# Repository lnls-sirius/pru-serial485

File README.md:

## PRUserial485 - _SIRIUS_
_PRU-based high performance serial communication_  

_Author:_  
Patricia H. Nallin ( _patricia.nallin@lnls.br_ )

_____

### Dependancies

* uio_pruss module
* prussdrv C library

_____

### Memory mapping

This applications reserves 2 MB from DDR memory via modprobe uio_pruss.
* 400 kB for sync curves
* 600 kB for FF application
* 1 MB for future needs

_____

### Building the library

Enter the folder `src` and run `make install`. This will compile PRU and host codes, install it to your Beaglebone and create a Python module to use these libraries.

_____

### Using the library

_**Before using it**_

1. Configure Beaglebone pins to PRU. Run `overlay.sh` script each time you restart your Beaglebone.

2. In your python-sirius (python3) code, you can just:
```python
import PRUserial485
```  
 It is not needed to copy any library files to your project.

---

#### Available Methods

_**General Purpose**_

- ```PRUserial485_open(int baudrate, char mode)```

   PRU initialization. Shared memory configuration and loading binaries into PRU.  
   * _baudrate:_  
   RS485 serial desired baudrate. Available: 9600, 14400, 19200, 38400, 57600, 115200 bps and 1, 6, 10, 12 Mbps
   * _mode:_  
   "M" for master, "S" for slave mode, and "P" for passive mode (receive-only, can never transmit).

- ```PRUserial485_address()```

   Gets SERIALxxCON board address (hardware defined)
   Returns: integer value (0 to 31)

- ```PRUserial485_close()```

   Closes PRUs and memory mapping.

- ```PRUserial485_write(bytes, float timeout)```

   Sending data through RS485 network  

   _*Parameters*_
  * _data:_  
  Python bytes containing values to be transmitted through serial network.
  * _timeout:_  
  Maximum waiting time to start getting an answer, in milliseconds (ms). Minimum: 15ns / Maximum: 64s. If 0, does not wait for response. ATTENTION: in slave mode, this parameter is ignored.  

  _*Return*_
  * _MASTER MODE:_  
   Returns only after response received (valid response, timeout or ignored)
  * _SLAVE MODE:_  
   Returns just after data completely sent.
  * _PASSIVE MODE:_  
   Always returns `ERR_PASSIVE_MODE_NO_SEND` immediately, without touching the bus. A passive-mode connection can never transmit; open in master or slave mode to send.

- ```PRUserial485_read(uint32_t nbytes)```

   Receiving data through RS485 network

   _*Parameters*_
  * _nbytes (OPTIONAL):_  
  Number of bytes to read. If empty or 0, all data will be read.
  If nbytes is greater than available bytes, return all available bytes. Note: This function does not block or wait for incoming data.   

   _*Return*_: bytes corresponding to data received.

- ```PRUserial485_read_flush()```

   Flush receive FIFO buffer.

_**Curves**_

- ```PRUserial485_curve(int block, [float_list curve1, float_list curve2, float_list curve3, float_list curve4])```

   Storing curves into memory. Each curve correspond to a power supply in the crate.   

   _*Parameters*_
  * _curveX:_  
  Python float list containing curve points, up to 6250 points. Curves must all have same length.
  * _block:_  
  Identification of block which will be loaded with curve points. (0 to 3)  

- ```PRUserial485_set_curve_block(int block)```

   Selection of block which will be performed in next cycle. Default value is 0.   

   _*Parameters*_
  * _block:_  
  Identification of block (0 to 3)  

- ```PRUserial485_read_curve_block()```

   Read block identification which will be performed in next cycle.    

   _*Returns*_: Block identification (0 to 3)

- ```PRUserial485_set_curve_pointer(int next_point)```

   Selection of point of curve that will be performed after the next sync pulse   

   _*Parameters*_
  * _next_point:_  
   index of next point (0 to (len(curve)-1))  

- ```PRUserial485_read_curve_pointer()```

   Read curve index (point) which will be sent in next sync pulse.    

   _*Returns*_: index of next point (0 to (len(curve)-1))

_**Sync Operation**_

- ```PRUserial485_sync_start(int sync_mode, float delay, int sync_address)```

   Sync mode operation.   

   _*Parameters*_
  * _sync_mode:_  
                 | 0x51 - Single curve sequence & Intercalated read messages  
                 | 0x5E - Single curve sequence & Read messages at End of curve  
                 | 0xC1 - Continuous curve sequence & Intercalated read messages  
                 | 0xCE - Continuous curve sequence & Read messages at End of curve  
                 | 0x5B - Single Sequence - Single Broadcast Function command
  * _delay:_  
  time between end of sync serial message and start of a normal message, when sending normal commands after sync pulses.
  * _sync_address:_  
  PS Controller address to which setpoints will be addressed to. Parameter only needed if sync_mode != 0x5B  

- ```PRUserial485_sync_stop()```

   Stops sync operation mode.   

- ```PRUserial485_sync_status()```

   Verifies whether PRU is waiting for a sync pulse or not    

   _*Returns*_: 1 if true, 0 if false

- ```PRUserial485_read_pulse_count_sync()```

   Read number of sync pulses already received.    

   _*Returns*_: counting value (0 to (2^32 - 1))

- ```PRUserial485_clear_pulse_count_sync()```

   Clears pulse counting registers. Action is only performed if sync mode is disabled.

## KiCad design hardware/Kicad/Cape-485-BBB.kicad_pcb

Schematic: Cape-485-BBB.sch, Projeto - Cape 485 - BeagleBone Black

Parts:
Beagle1: BeagleBone
C3, C4, C6, C7, C13: 0.1uF; C_0805
C5, C15: 1uF; C_0805
C8: 0.01uF; C_0805
C9, C11: 47n; C_0805
C10: 10u; C_0805
C12: Conn_SMA; SMA_Small
C14: 2.2uF; C_0805
C16: 100n; C_0805
D1: Led_Small; LED-0805
D2, D3, D4: LED; LED_0805
J1, J2: RJ25
JP3, JP4: Jumper_NO_Small; Test_Point
P10: CONN_02X05; Pin_Header_Straight_2x05
Q1, Q2, Q3: BSR14; SOT-23
R1: 50r; R_0805
R2, R9, R11: 1k; R_0805
R3: 620R; R_0805
R4, R8: 150r; R_0805
R10: 120r; R_0805
R12, R14, R16: 10k; R_0805
R13, R15, R17: 100r; R_0805
U1: MAX3107E; TSSOP-24_4.4x7.8mm_Pitch0.65mm
U3: IL3685; SOIC-16_7.5x10.3mm_Pitch1.27mm
U4: DCR01XXXXU; SOIC-28_7.5x17.9mm_Pitch1.27mm
U5, U6: TS5A21366
X1: OSCILADOR; Oscilador_3.3V_HCMOS_TTL_SMD

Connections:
+3V3: Beagle1.C3, Beagle1.C4, C3.1, C4.1, C6.2, C8.1, C9.2, P10.1, P10.3, P10.5, P10.7, P10.9, R2.1, U1.3 (Va), U1.5 (I2C'/SPI), U1.6 (LDOEN), U1.13 (VL), U1.23 (Vext), U3.1 (VDD1), X1.4 (VCC)
+5V: Beagle1.C7, Beagle1.C8, C14.1, D2.2 (A), D3.2 (A), D4.2 (A), R3.1, U4.1 (Vs), U4.2 (Vs)
+5VP: C10.1, C11.2, C13.1, C16.2, JP3.1, JP4.1, R4.2, U3.16 (VDD2), U4.14 (Vo), U5.8 (V+)
/1: Beagle1.B31, P10.2
/2: Beagle1.B32, P10.4
/4: Beagle1.B33, P10.6
/8: Beagle1.B34, P10.8
/16: Beagle1.B35, P10.10
/A: J1.2, J2.2, U3.12 (A), U5.2 (COM1)
/B: J1.3, J2.3, U3.13 (B), U5.5 (NO2)
/CTS': U1.19 (CTS'), U1.20 (RTS'/CLKOUT), U3.4 (RE), U3.5 (DE)
/LED1: Beagle1.B28, R12.2
/LED2: Beagle1.B29, R14.2
/LED3: Beagle1.B40, R16.2
/PRU0: Beagle1.B39, R2.2, U1.11 (IRQ')
/PRU2: Beagle1.B41, U1.10 (DIN/A1)
/PRU4: Beagle1.B43, U1.9 (CS'/A0)
/PRU6: Beagle1.B45, U1.8 (SCLK/SCL)
/PRU7: Beagle1.B46, U1.7 (DOUT/SDA)
/RX: U1.21 (RX), U3.3 (R)
/SYNC: Beagle1.B27, C12.1, R1.1
/SYS_RST: Beagle1.C10, C7.2, U1.12 (RST)
/TX: U1.22 (TX), U3.6 (D)
GNDA: Beagle1.B1, Beagle1.B2, Beagle1.C45, Beagle1.C46, C3.2, C4.2, C5.2, C6.1, C7.1, C8.2, C9.1, C12.2, C14.2, D1.1 (K), Q1.3 (E), Q2.3 (E), Q3.3 (E), R1.2, U1.2 (AGND), U1.14 (DGND), U3.2 (gnd1), U3.8 (gnd1), U4.26 (0VIN), U4.27 (0VIN), X1.2 (GND)
GNDREF: C10.2, C11.1, C13.2, C15.2, C16.1, J1.1, J1.4, J1.5, J2.1, J2.4, J2.5, R8.1, R9.2, R11.2, U3.9 (gnd2), U3.15 (gnd2), U4.13 (0VOUT), U5.4 (GND)
unnamed: C5.1, U1.4 (V18)
unnamed: C15.1, U4.12 (VREC), U4.16 (ENABLE)
unnamed: D1.2 (A), R3.2
unnamed: D2.1 (K), R13.1
unnamed: D3.1 (K), R15.1
unnamed: D4.1 (K), R17.1
unnamed: JP3.2, R9.1, U5.3 (IN2), U5.7 (IN1)
unnamed: JP4.2, R11.1
unnamed: Q1.1 (C), R13.2
unnamed: Q1.2 (B), R12.1
unnamed: Q2.1 (C), R15.2
unnamed: Q2.2 (B), R14.1
unnamed: Q3.1 (C), R17.2
unnamed: Q3.2 (B), R16.1
unnamed: R4.1, U5.1 (NO1)
unnamed: R8.2, U5.6 (COM2)
unnamed: U1.1 (XIN), X1.3 (OUT)

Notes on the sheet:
TERMINACAO 485
ENDERECO (MODO SLAVE)
Alimentação Isolada

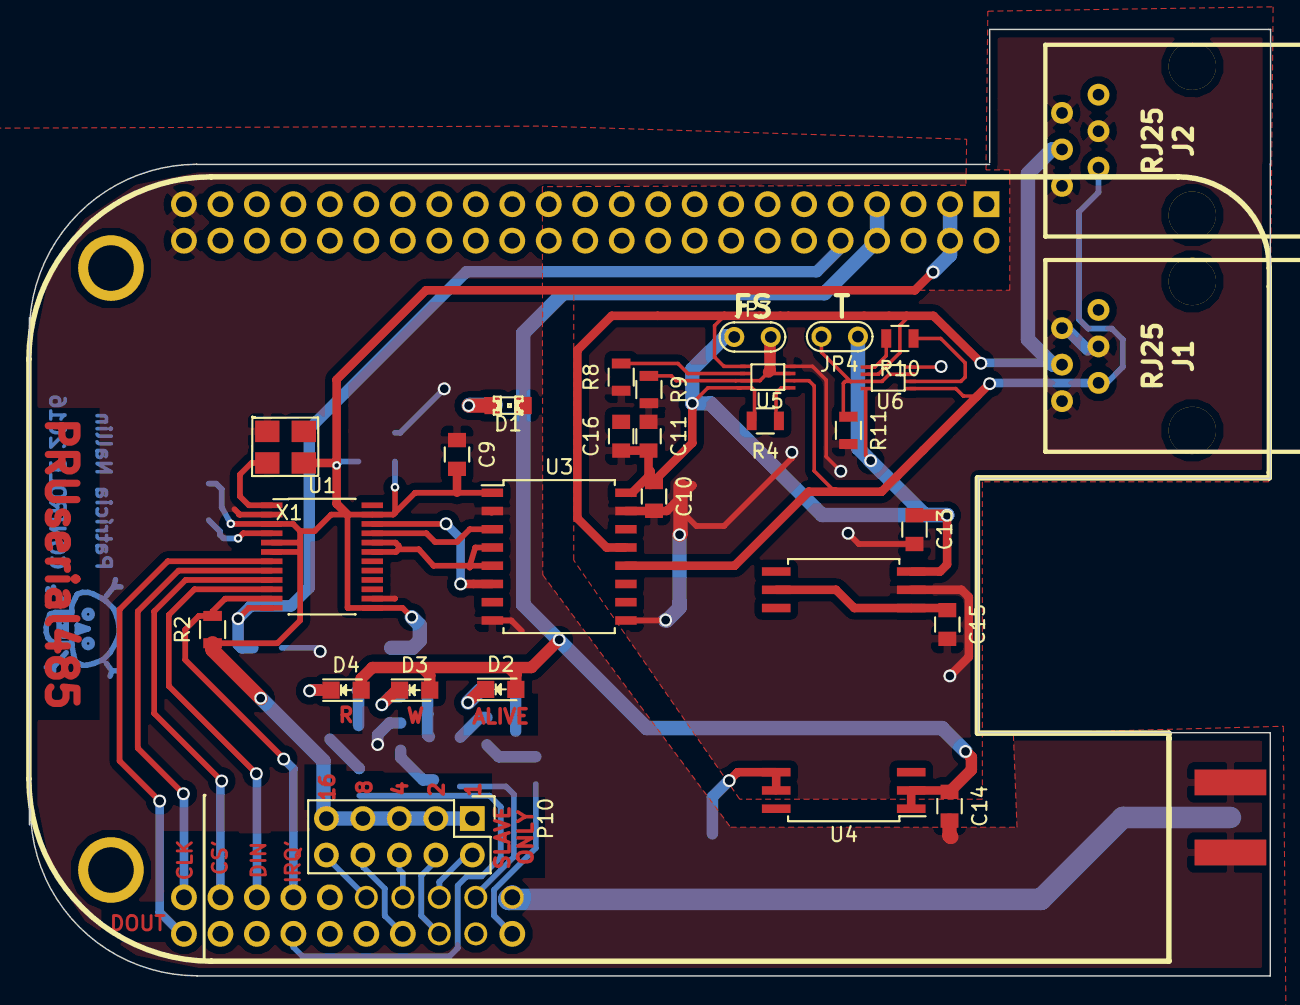
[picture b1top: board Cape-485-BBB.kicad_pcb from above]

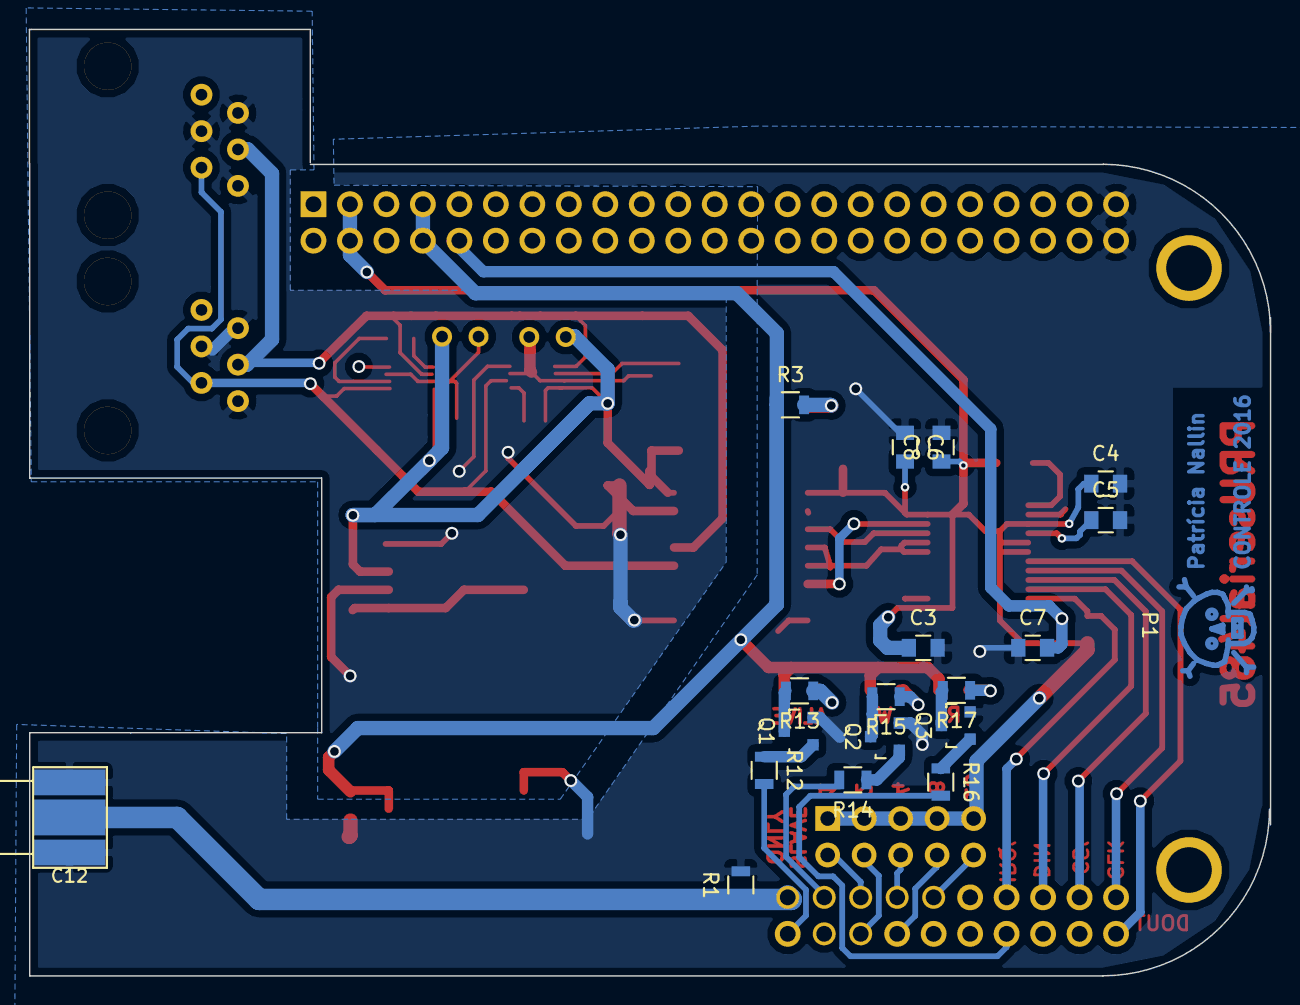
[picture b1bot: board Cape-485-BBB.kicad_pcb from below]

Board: 2 copper layers, 86.4 x 65.9 mm, 48 parts (19 on the bottom side), 42 nets.

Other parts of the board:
P1: CONN_01X01; Symbol_Danger_CopperTop_Small

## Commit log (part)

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2015-08-17 second commit
2015-08-17 Teste
2015-08-17 PRU commit 1
2015-08-17 PRU commit 2
2015-08-18 PRU firmware
2015-08-19 PRU firmware - BUG comando iniciar post-morten corrigido
2015-08-19 PRU firmware - Comando 08 corrigido / include adicionado / timeout em alto nivel
2015-08-20 PRU firmware atualizado
2015-08-20 Novo documento
2015-08-31 sync - borda de subida
2015-08-31 sync
2015-10-27 testing
2015-10-27 Hardware docs
2015-10-27 sem uso
2015-11-19 Nova versao: Serial485 Modo Master ou Slave
2015-12-10 Atulizado - linha de atualizacao do byte shram[1]
2015-12-10 update linha 423
2016-05-30 new hardware version
2016-05-30 new firmware version
2016-05-30 new installation doc version
2016-07-19 Update DTO for BBB and BBG
2016-08-12 added panels design
2016-08-31 Sync pulse counting added
2016-08-31 not necessasry
2016-08-31 not necessary
2016-11-04 Added info about timeout range
2016-11-04 Improving slave data transfer
2016-11-06 upgrades
2017-01-30 Minor changes on PRUserial485.p
2017-02-03 New performance for sync mode
2017-02-03 update data type on write method
2017-02-07 Update for choosing when to send normal messages on sync mode.
2017-02-07 Update sync and normal messages delay
2017-02-07 Update sync_start parameter
2017-02-07 Update for choosing time between sync and normal commands
2017-02-08 Update sync delay for usec
2017-02-08 PRUserial485_write. request must be a list of char
2017-02-08 Update sync instruction. Broadcasting (0xFF) function 12.
2017-02-21 Sync count on slave mode added.
2017-02-21 Update sync count for slave mode.
2017-02-22 Board hardware address updated. No more conflict.
2017-03-03 Update send function. Timeout type conversion is ok now
2017-03-22 Update PRUserial485_read(). Returns empty vector if buffer contains old data.
2017-03-22 Update set_sync_stop_PRU() function.
2017-04-28 Update Slave Receive instructions: Removed blinking LED and reads bytes in blocks of 16.
2017-04-28 New organizing folders and Python library is now installed on system
2017-05-03 setup.py added.
2017-05-25 Update error return on function "clear_pulse_count_sync()"
2018-01-25 Updated PRUserial485 library. Sync via setpoint and Python3 compatibility
2018-01-26 README file
2018-01-26 Test commit
2018-01-29 Update script to use sirius-python link
2018-01-29 Add gitignore file
2018-01-30 Adapt PRUserial485.py to pylama code conventions
2018-03-27 New version available
2018-04-10 Add __version__ attribute to package
    - this attribute is read from VERSION file and set.
    - rename PRUserial485.py to implementation.py to avoid package and module having the same name, thus avoiding potential problems.
    - Change return value of 'sync_status' to boolen type, instead of string.
2018-04-13 New version available. Updating curves on the fly in now implemented
2018-04-13 Minor changes
2018-04-14 Replace tab chars to spaces in python module
    - in order to avoid identation runtime error.
2018-04-14 Create a python module variable 'libraries_loaded'
    - to indicate whether all dynamical low-level PRU libraries were successfully loaded
    - catching the exception while ctype-importing the libraries allow for the PRUserial485 python library importation to happen in those situations where the PRU functions would never be invoked (simula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
2018-04-14 Clean package namespace
2018-04-17 Read me - first version
2018-04-17 Read me - first version available
2018-04-19 updating .sh scripts
2018-04-20 Add commit hash to package version
    - Add input to library_build.sh so that user can select 'install' (default if argument is not passed) or 'develop' for the python library.
2018-04-20 RS485 delay after sync pulse for 0x5C mode added
2018-04-27 Block # (curves) is now read at the beginning of curve
2018-04-27 Add *swp to gitignore
2018-04-28 Replace tabs for spaces in C files
2018-04-28 Comment out print statements in C code
    - Instead of print statements, we can use return values and a constant table
    to infer what the error was.
    - Fixed code identation.
2018-04-28 Add python namespace for return constants of C lib
2018-04-28 Fix bug introduced in last commit
2018-04-28 Add return codes table in C file too
2018-04-28 Minor code cleanup
2018-04-28 Fix conflict from last commit
2018-04-28 Code cleanup
    - Move table of return codes from .c to .h file
    - Sort order of fcuntions in .h according to order in .c
    - Added missing return docstrings in .h file.
2018-05-02 Bug corretions on signaling end of sync mode
2018-05-02 Change minor part of version number (bug fix)
2018-05-17 Changing sync mode code 0x5C to 0x5B
2018-05-17 Sync mode 0x5C moved to 0x5B
2018-05-17 README updated
2018-05-17 Update constants in python package
    - Update also code comments and docs with new sync mode code.
2018-05-17 Update bug-fix portion of package version number
2018-08-09 Both Python-Sirius and Python2 library building is now available
2018-09-20 new developments backup
2019-01-30 Bug correction on PRUserial485 high level library
    Bug on function PRUserial485_set_curve_pointer(int). Comparison before returning was always locking, once values were never identical (missing multiplication x16)
2019-08-06 Bug correction: commit hash at library version
2020-01-10 Improving python module performance
2020-01-13 renaming and improving prucon to pru-serial485
2020-01-13 hash version included
2020-01-13 code comments added
2020-01-13 first developments
2020-01-14 minor bugs correction
2020-01-21 Complete python module and README file
2020-01-28 new developments. Cycle buffer also in PRU
2020-01-29 beautifying codes
2020-02-04 Mutex added and increasing py recv buffer
2020-02-06 Create teste
2020-02-11 improving performande
2020-04-16 flush recv fifo
2020-05-18 removing python2
2020-05-18 version tag 1.5.0
2020-05-18 update date
2020-06-24 new version for FF correctors
2020-06-25 dev files
2020-07-01 ff quadratura
2020-07-06 new version, initial state automatic
2020-07-21 Create Makefile
2020-09-11 resolving bugs
2020-09-16 removing .save file
2020-09-18 new files
2023-08-09 Wiki infos
2024-05-27 files for new ff
2024-07-16 PRUserial485{lib,.c,.h}: Add max ID range in config function
2024-07-16 PRUserial485.c: printfs and spaces removed, minor changes
2024-07-16 PRUserial485{lib,.c,.h}: New functions for status, table size, current table and pointer
2024-07-19 read current position function
2024-07-19 PRUserial485.c: remove print and change casting from int to int16_t
2024-07-19 VERSION: 1.7.0
2024-07-31 Support 1Mbps baudrate
2024-08-08 Improve resource sharing for ARM/secondary PRU (FF) and add a file for shram mapping
2024-09-10 Add flags for ff application
2024-09-10 Comment on library functions
2024-10-11 Cleaner repository: ff aplication detached and available at CNPEM GitLab
2024-10-17 Update doc files
2025-11-28 Fix OFFSET_SHRAM_READ reference in comments
    The documentation in the comments stated that the receive-data offsets
    started at 6000, but `OFFSET_SHRAM_READ` is defined as `0x1800` (6144
    in decimal). This commit updates the comments to reflect the correct
    offset value.
2026-04-09 update feedforward min/max range offsets
    This commit defines a feedforward minimum offset (SHRAM_OFFSET_MIN_RANGE)
    in the BeagleBone shared memory. It also updates the maximum offset (SHRAM_OFFSET_FF_MAX_RANGE).
    These changes repurpose previously unused offsets and were made to reflect a recent change in
    the FeedForward configuration that now also receives a minimum value.
